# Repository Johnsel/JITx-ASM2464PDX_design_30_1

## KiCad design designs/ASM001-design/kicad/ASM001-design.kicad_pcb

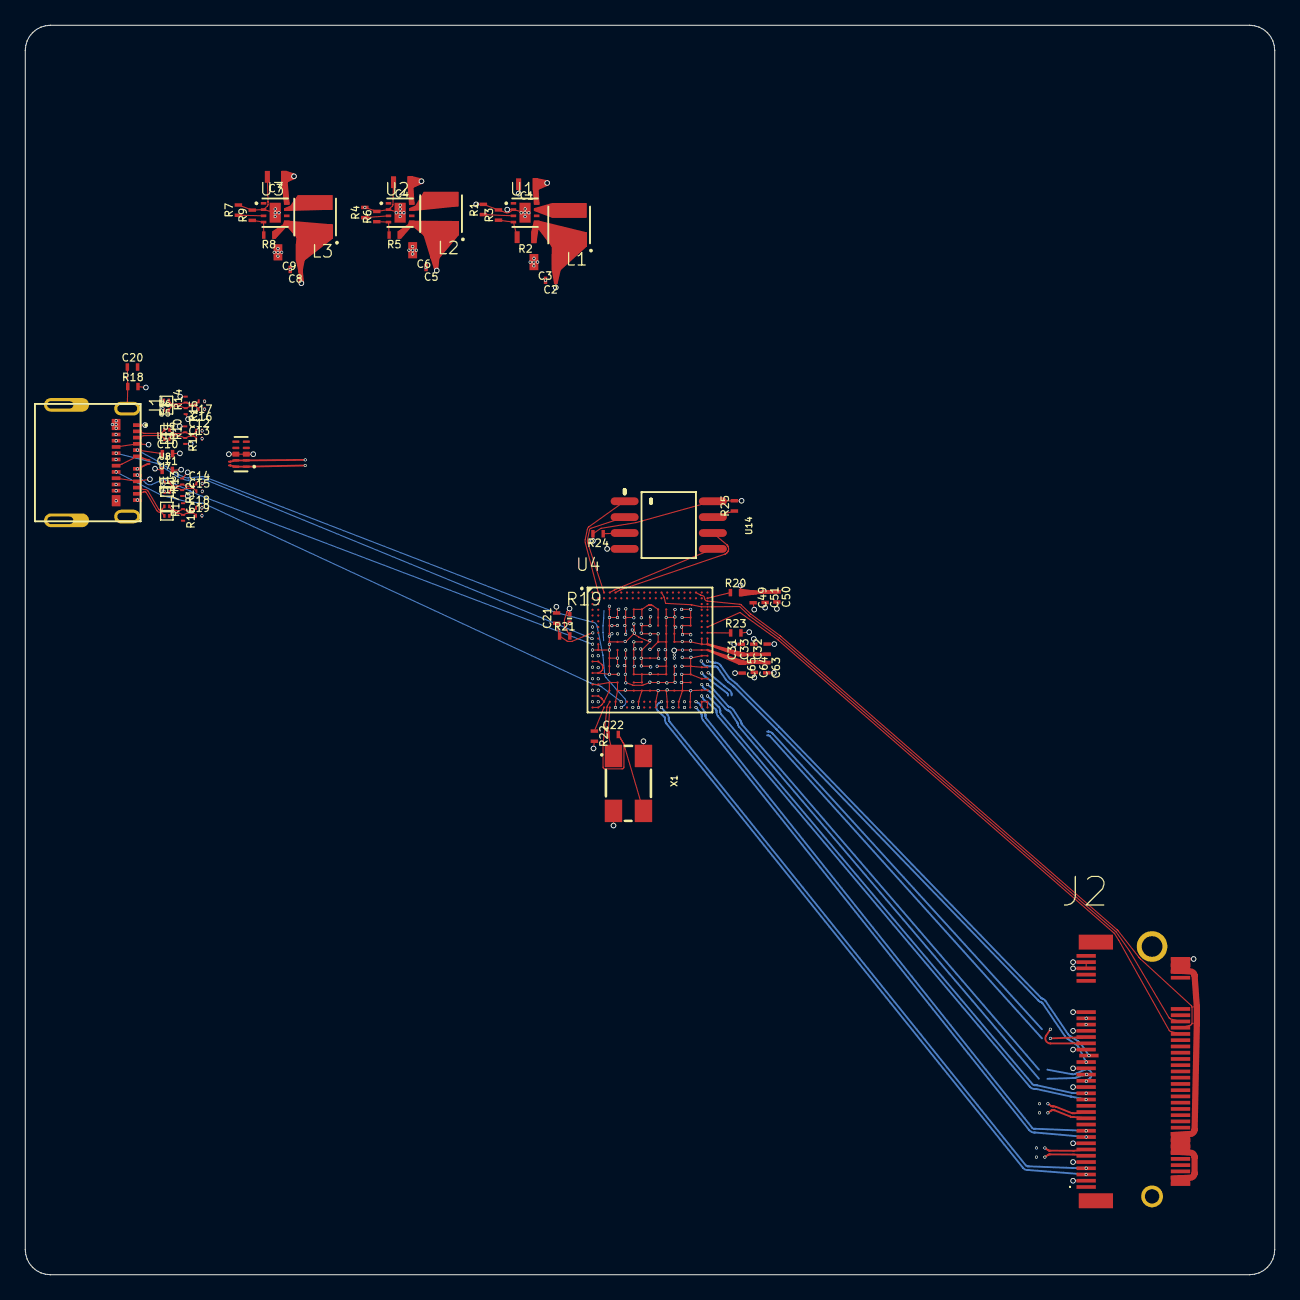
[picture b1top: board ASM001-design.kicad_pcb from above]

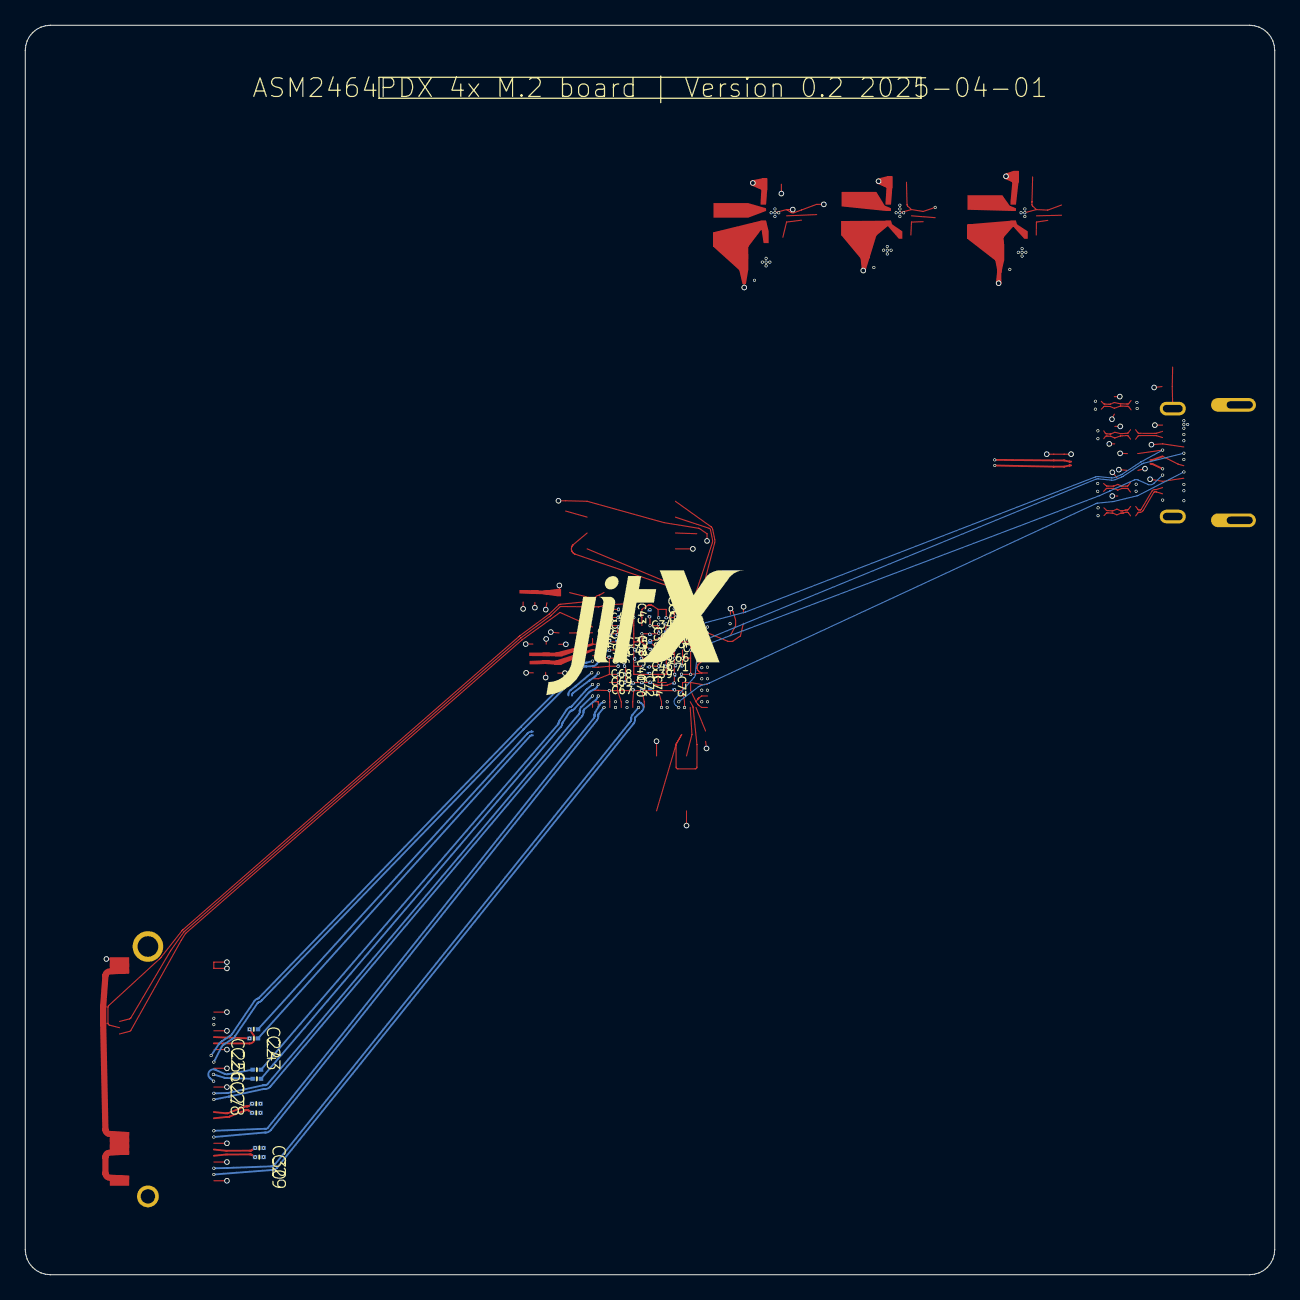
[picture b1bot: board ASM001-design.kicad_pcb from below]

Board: 6 copper layers, 100.0 x 100.0 mm, 123 parts (47 on the bottom side), 88 nets.

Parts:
C1: 10u; Pkg0603_3
C2: 4.7n; Pkg0402_1
C3: 22u; Pkg0805
C4: 10u; Pkg0603
C5: 4.7n; Pkg0402_4
C6: 22u; Pkg0805_1
C7: 10u; Pkg0603_1
C8: 4.7n; Pkg0402_6
C9: 22u; Pkg0805_2
C10, C11: 2.2n; Pkg0402_18
C12, C13, C14, C15: 220n; Pkg0201_3
C16, C17, C18, C19: 470n; Pkg0201_5
C20: 4.7n; Pkg0402_2
C21: 1u; Pkg0402_10
C22: 10p; LP_1
C23, C24, C25, C26, C27, C28, C29, C30: 220p; SMT_0201
C31, C32, C33: 10u; Pkg0402_12
C34, C35, C36, C37, C38, C39, C40, C41, C42, C43, C44: 2.2u; Pkg0201_6
C45, C46, C47, C48: 220n; Pkg0201_2
C49, C50, C51: 10u; Pkg0402_3
C52, C53, C54, C55, C56, C57, C58, C59, C60, C61, C62: 2.2u; Pkg0201_4
C63, C64, C65: 10u; Pkg0402
C66, C67, C68, C69, C70, C71, C72, C73, C74, C75, C76: 2.2u; Pkg0201_1
J1: 2012670005; USB_TYPE_C_CONNECTOR
J2: 1-2199230-6; LP_1_2199230_6
JITX1: non-BOM; JITX_SM_LP
L1, L2, L3: 1u; MOLDED
R1: 0R; Pkg0402_7
R2: 26K1; Pkg0603_2
R3: 4K12; Pkg0402_11
R4: 0R; Pkg0402_9
R5: 13K3; Pkg0402_13
R6: 4K12; Pkg0402_16
R7: 0R; Pkg0402_14
R8: 6K2; Pkg0402_17
R9: 4K12; Pkg0402_19
R10, R11, R12, R13, R14, R15, R16, R17: 200K; Pkg0201
R18: 0R; Pkg0402_20
R19: 0R; SMT_0201_1
R20, R23, R24, R25: 4K7; Pkg0402_5
R21: 100K; Pkg0402_8
R22: 12K1; Pkg0402_15
TXT1: ASM2464PDX 4x M.2 board | Version 0.2 2025-04-01; TEXT_LP
U1, U2, U3: TPS62082DSG; SON50P200X200_9N
U4: ASM2464PDX; BGA273N46P21X21_1000X1000X98
U5, U6, U7, U8, U9, U10, U11, U12: ESD132-B1-W0201 E6327; WLL_2_3_L0_6_W0_3_P0_36_BI
U13: ESD224DQAR; USON_10
U14: W25Q32JVSSIQ; LP_2
X1: ABMM2-25.000MHZ-D1-T; LP

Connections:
C_p1: C20.1, J1.M1, J1.M2, J1.M3, J1.M4, R18.1
FB: R5.2, R6.1, U2.4
GND: C1.2, C2.2, C3.2, C4.2, C5.2, C6.2, C7.2, C8.2, C9.2, C10.2, C11.2, C20.2, C21.2, C31.2, C32.2, C33.2, C34.2, C35.2, C36.2, C37.2, C38.2, C39.2, C40.2, C41.2, C42.2, C43.2, C44.2, C45.2, C46.2, C47.2, C48.2, C49.2, C50.2, C51.2, C52.2, C53.2, C54.2, C55.2, C56.2, C57.2, C58.2, C59.2, C60.2, C61.2, C62.2, C63.2, C64.2, C65.2, C66.2, C67.2, C68.2, C69.2, C70.2, C71.2, C72.2, C73.2, C74.2, C75.2, C76.2, J1.A1, J1.A12, J1.B1, J1.B12, J2.3, J2.9, J2.15, J2.33, J2.39, J2.45, J2.51, J2.57, J2.71, J2.73, R1.2, R3.2, R4.2, R6.2, R7.2, R9.2, R10.2, R11.2, R12.2, R13.2, R14.2, R15.2, R16.2, R17.2, R18.2, R22.2, R23.2, U1.2, U1.9, U2.2, U2.9, U3.2, U3.9, U4.AA1, U4.AA2, U4.AA5, U4.AA9, U4.AA12, U4.AA14, U4.AA16, U4.AA18, U4.AA20, U4.AA21, U4.D4, U4.D5, U4.D11, U4.D17, U4.D18, U4.E4, U4.E5, U4.E17, U4.E18, U4.F4, U4.F5, U4.F8, U4.F17, U4.F18, U4.H4, U4.H8, U4.H17, U4.H18, U4.J4, U4.J5, U4.J6, U4.J11, U4.K2, U4.L1, U4.L2, U4.L4, U4.L5, U4.L9, U4.L13, U4.M20, U4.M21, U4.N1, U4.N2, U4.N4, U4.N5, U4.N9, U4.N11, U4.N13, U4.N17, U4.N18, U4.P4, U4.P5, U4.P9, U4.P11, U4.P17, U4.P18, U4.P20, U4.P21, U4.R1, U4.R2, U4.T4, U4.T5, U4.T17, U4.T18, U4.T20, U4.T21, U4.U1, U4.U2, U4.U4, U4.U5, U4.U17, U4.U18, U4.V4, U4.V5, U4.V6, U4.V8, U4.V9, U4.V11, U4.V13, U4.V14, U4.V16, U4.V17, U4.V18, U4.V20, U4.V21, U4.W1, U4.W2, U4.Y3, U4.Y5, U4.Y9, U4.Y12, U4.Y14, U4.Y16, U4.Y18, U4.Y20, U4.Y21, U13.3, U13.8, U14.4, X1.2, X1.4
IC_SW_FB: R2.2, R3.1, U1.4
IC_SW_MODE: R7.1, U3.3
MODE: R1.1, U1.3
RST#: C21.1, R21.1, U4.H1
SHIELD: J2.MP1, J2.MP2
SPI_CLK: U4.A5, U14.6
SPI_CS#: U4.A2, U14.1
SPI_DI: U4.A4, U14.5
SPI_DO: U4.A3, U14.2
SPI_IO2: R24.1, U14.3
SPI_IO3: R25.1, U14.7
SW-NODE: L1.c, U1.7
SW-NODE1: L3.c, U3.7
SW-NODE2: L2.c, U2.7
SW_FB: R8.2, R9.1, U3.4
SW_MODE: R4.1, U2.3
TEST_EN: R23.1, U4.H21
UART_TX: R20.1, U4.B21
UREXT: R22.1, U4.AA3
VBUS: C1.1, C4.1, C7.1, J1.A4, J1.A9, J1.B4, J1.B9, U1.8, U2.8, U3.8, U4.G1
VCCA33: R19.2, U4.H5
VCCH: C2.1, C3.1, C49.1, C50.1, C51.1, C52.1, C53.1, C54.1, C55.1, C56.1, C57.1, C58.1, C59.1, C60.1, C61.1, C62.1, J2.2, J2.4, J2.12, J2.14, J2.16, J2.18, J2.70, J2.72, J2.74, L1.a, R2.1, R19.1, R20.2, R21.2, R24.2, R25.2, U1.5, U4.D6, U4.D8, U4.D9, U4.D13, U4.E6, U4.E8, U4.E9, U4.E13, U4.F6, U4.F13, U4.H6, U14.8
VCCL: C5.1, C6.1, C63.1, C64.1, C65.1, C66.1, C67.1, C68.1, C69.1, C70.1, C71.1, C72.1, C73.1, C74.1, C75.1, C76.1, L2.a, R5.1, U2.5, U4.L6, U4.L16, U4.L17, U4.L18, U4.L20, U4.L21, U4.N6, U4.N16, U4.P6, U4.P16, U4.T6, U4.T16, U4.U6, U4.U11, U4.U13, U4.U14, U4.U16
VDD: C8.1, C9.1, C31.1, C32.1, C33.1, C34.1, C35.1, C36.1, C37.1, C38.1, C39.1, C40.1, C41.1, C42.1, C43.1, C44.1, C45.1, C46.1, C47.1, C48.1, L3.a, R8.1, U3.5, U4.D14, U4.D16, U4.E11, U4.E14, U4.E16, U4.F9, U4.F11, U4.F14, U4.F16, U4.H9, U4.H11, U4.H13, U4.H14, U4.H16, U4.J8, U4.J9, U4.J13, U4.J14, U4.J16, U4.J17, U4.J18, U4.J20, U4.J21, U4.K20, U4.K21, U4.L8, U4.L11, U4.L14, U4.N8, U4.N14, U4.P8, U4.P13, U4.P14, U4.T8, U4.T9, U4.T11, U4.T13, U4.T14, U4.U8, U4.U9
XI: C22.1, U4.AA4, X1.1
XO: C22.2, U4.Y4, X1.3
asm2464pdx_usb-c_data_N: J1.A7, J1.B7, U4.M2, U13.1, U13.10
asm2464pdx_usb-c_data_P: J1.A6, J1.B6, U4.M1, U13.2, U13.9
cc0: C10.1, J1.A5, U4.AA6
cc1: C11.1, J1.B5, U4.Y6
dst-ep_data_lane0_RX_N: J2.41, U4.N20
dst-ep_data_lane1_RX_P: J2.31, U4.W21
dst-ep_data_lane3_RX_P: J2.7, U4.AA13
dst-ep_data_refclk_N: J2.53, U4.Y8
dst-ep_data_refclk_P: J2.55, U4.AA8
sbu0: J1.A8, U4.K1
sbu1: J1.B8, U4.J1
src-ep_control_CLKREQ#: J2.52, U4.A19
src-ep_control_PERST#: J2.50, U4.G21
src-ep_control_PEWAKE#: J2.54, U4.A13
src-ep_data_lane0_RX_P: J2.43, U4.N21
src-ep_data_lane1_RX_N: J2.29, U4.W20
src-ep_data_lane2_RX_N: J2.17, U4.AA19
src-ep_data_lane2_RX_P: J2.19, U4.Y19
src-ep_data_lane3_RX_N: J2.5, U4.Y13
usb4_type_c_x_A_N: J1.A10, U12.1
usb4_type_c_x_A_N1: J1.B10, U10.2
usb4_type_c_x_A_N2: C14.1, R13.1, U8.2
usb4_type_c_x_A_N3: J1.B3, U8.1
usb4_type_c_x_A_N4: C13.1, R11.1, U5.2
usb4_type_c_x_A_N5: C18.1, R17.1, U12.2
usb4_type_c_x_A_N6: J1.A3, U5.1
usb4_type_c_x_A_P: J1.B2, U7.1
usb4_type_c_x_A_P1: C12.1, R10.1, U6.2
usb4_type_c_x_A_P2: J1.A2, U6.1
usb4_type_c_x_A_P3: C17.2, R14.1, U9.1
usb4_type_c_x_A_P4: J1.B11, U9.2
usb4_type_c_x_A_P5: J1.A11, U11.1
usb4_type_c_x_A_P6: C15.1, R12.1, U7.2
usb4_type_c_x_B_N: C13.2, U4.T2
usb4_type_c_x_B_N1: C14.2, U4.V1
usb4_type_c_x_B_N2: C16.1, U4.P2
usb4_type_c_x_B_N3: C18.2, U4.Y1
usb4_type_c_x_B_N4: C16.2, R15.1, U10.1
usb4_type_c_x_B_P: C19.2, U4.Y2
usb4_type_c_x_B_P1: C17.1, U4.P1
usb4_type_c_x_B_P2: C12.2, U4.T1
usb4_type_c_x_B_P3: C15.2, U4.V2
usb4_type_c_x_B_P4: C19.1, R16.1, U11.2
x_A_N: C24.1, U4.R21
x_A_N1: C25.2, U4.U21
x_A_N2: C29.1, U4.AA15
x_A_N3: C28.2, U4.AA17
x_A_P: C30.1, U4.Y15
x_A_P1: C23.1, U4.R20
x_A_P2: C26.2, U4.U20
x_A_P3: C27.2, U4.Y17
x_B_N: C29.2, J2.11
x_B_N1: C24.2, J2.47
x_B_N2: C28.1, J2.23
x_B_N3: C25.1, J2.35
x_B_P: C30.2, J2.13
x_B_P1: C27.1, J2.25
x_B_P2: C26.1, J2.37
x_B_P3: C23.2, J2.49

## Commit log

2025-01-30 Semi-working again
2025-02-01 Started routing
2025-02-01 Pre-rewrite
2025-02-01 Single M.2 crash)
2025-02-09 Current state
2025-02-10 Cleanup and fix a lot of topo issues. Finally routing with constraints applied
2025-02-10 Fetch newer jsl
2025-02-10 jlc-pcb updated
2025-02-10 Version bump
2025-02-12 USB4
2025-03-31 Updated some components and started constraining + routing
2025-03-31 Update to latest JSL
    Updated PCIe supports definitions in components
2025-03-31 Work in progress routing
2025-03-31 PCIe lanes routed
2025-03-31 PCIe lanes routed, caps and some USB remaining
2025-03-31 More USB routes
2025-03-31 Mostly routed, still needs decoupling caps underneath BGA
2025-03-31 Fully routed.
2025-03-31 Stable routing. Next item decoupling capacitors.
2025-04-01 First set of decoupling caps
2025-04-01 Third set of decoupling caps
2025-04-01 Last decoupling caps done
2025-04-01 Fixed some missing routes
2025-04-01 Added length matching
2025-04-01 Fixed some routes
2025-04-01 Some cleanup
2025-04-01 To do: stitch vias and stackup calculations
2025-04-01 Alpha point
2025-07-16 Added new board layout beginnings
2025-07-17 Partial design
